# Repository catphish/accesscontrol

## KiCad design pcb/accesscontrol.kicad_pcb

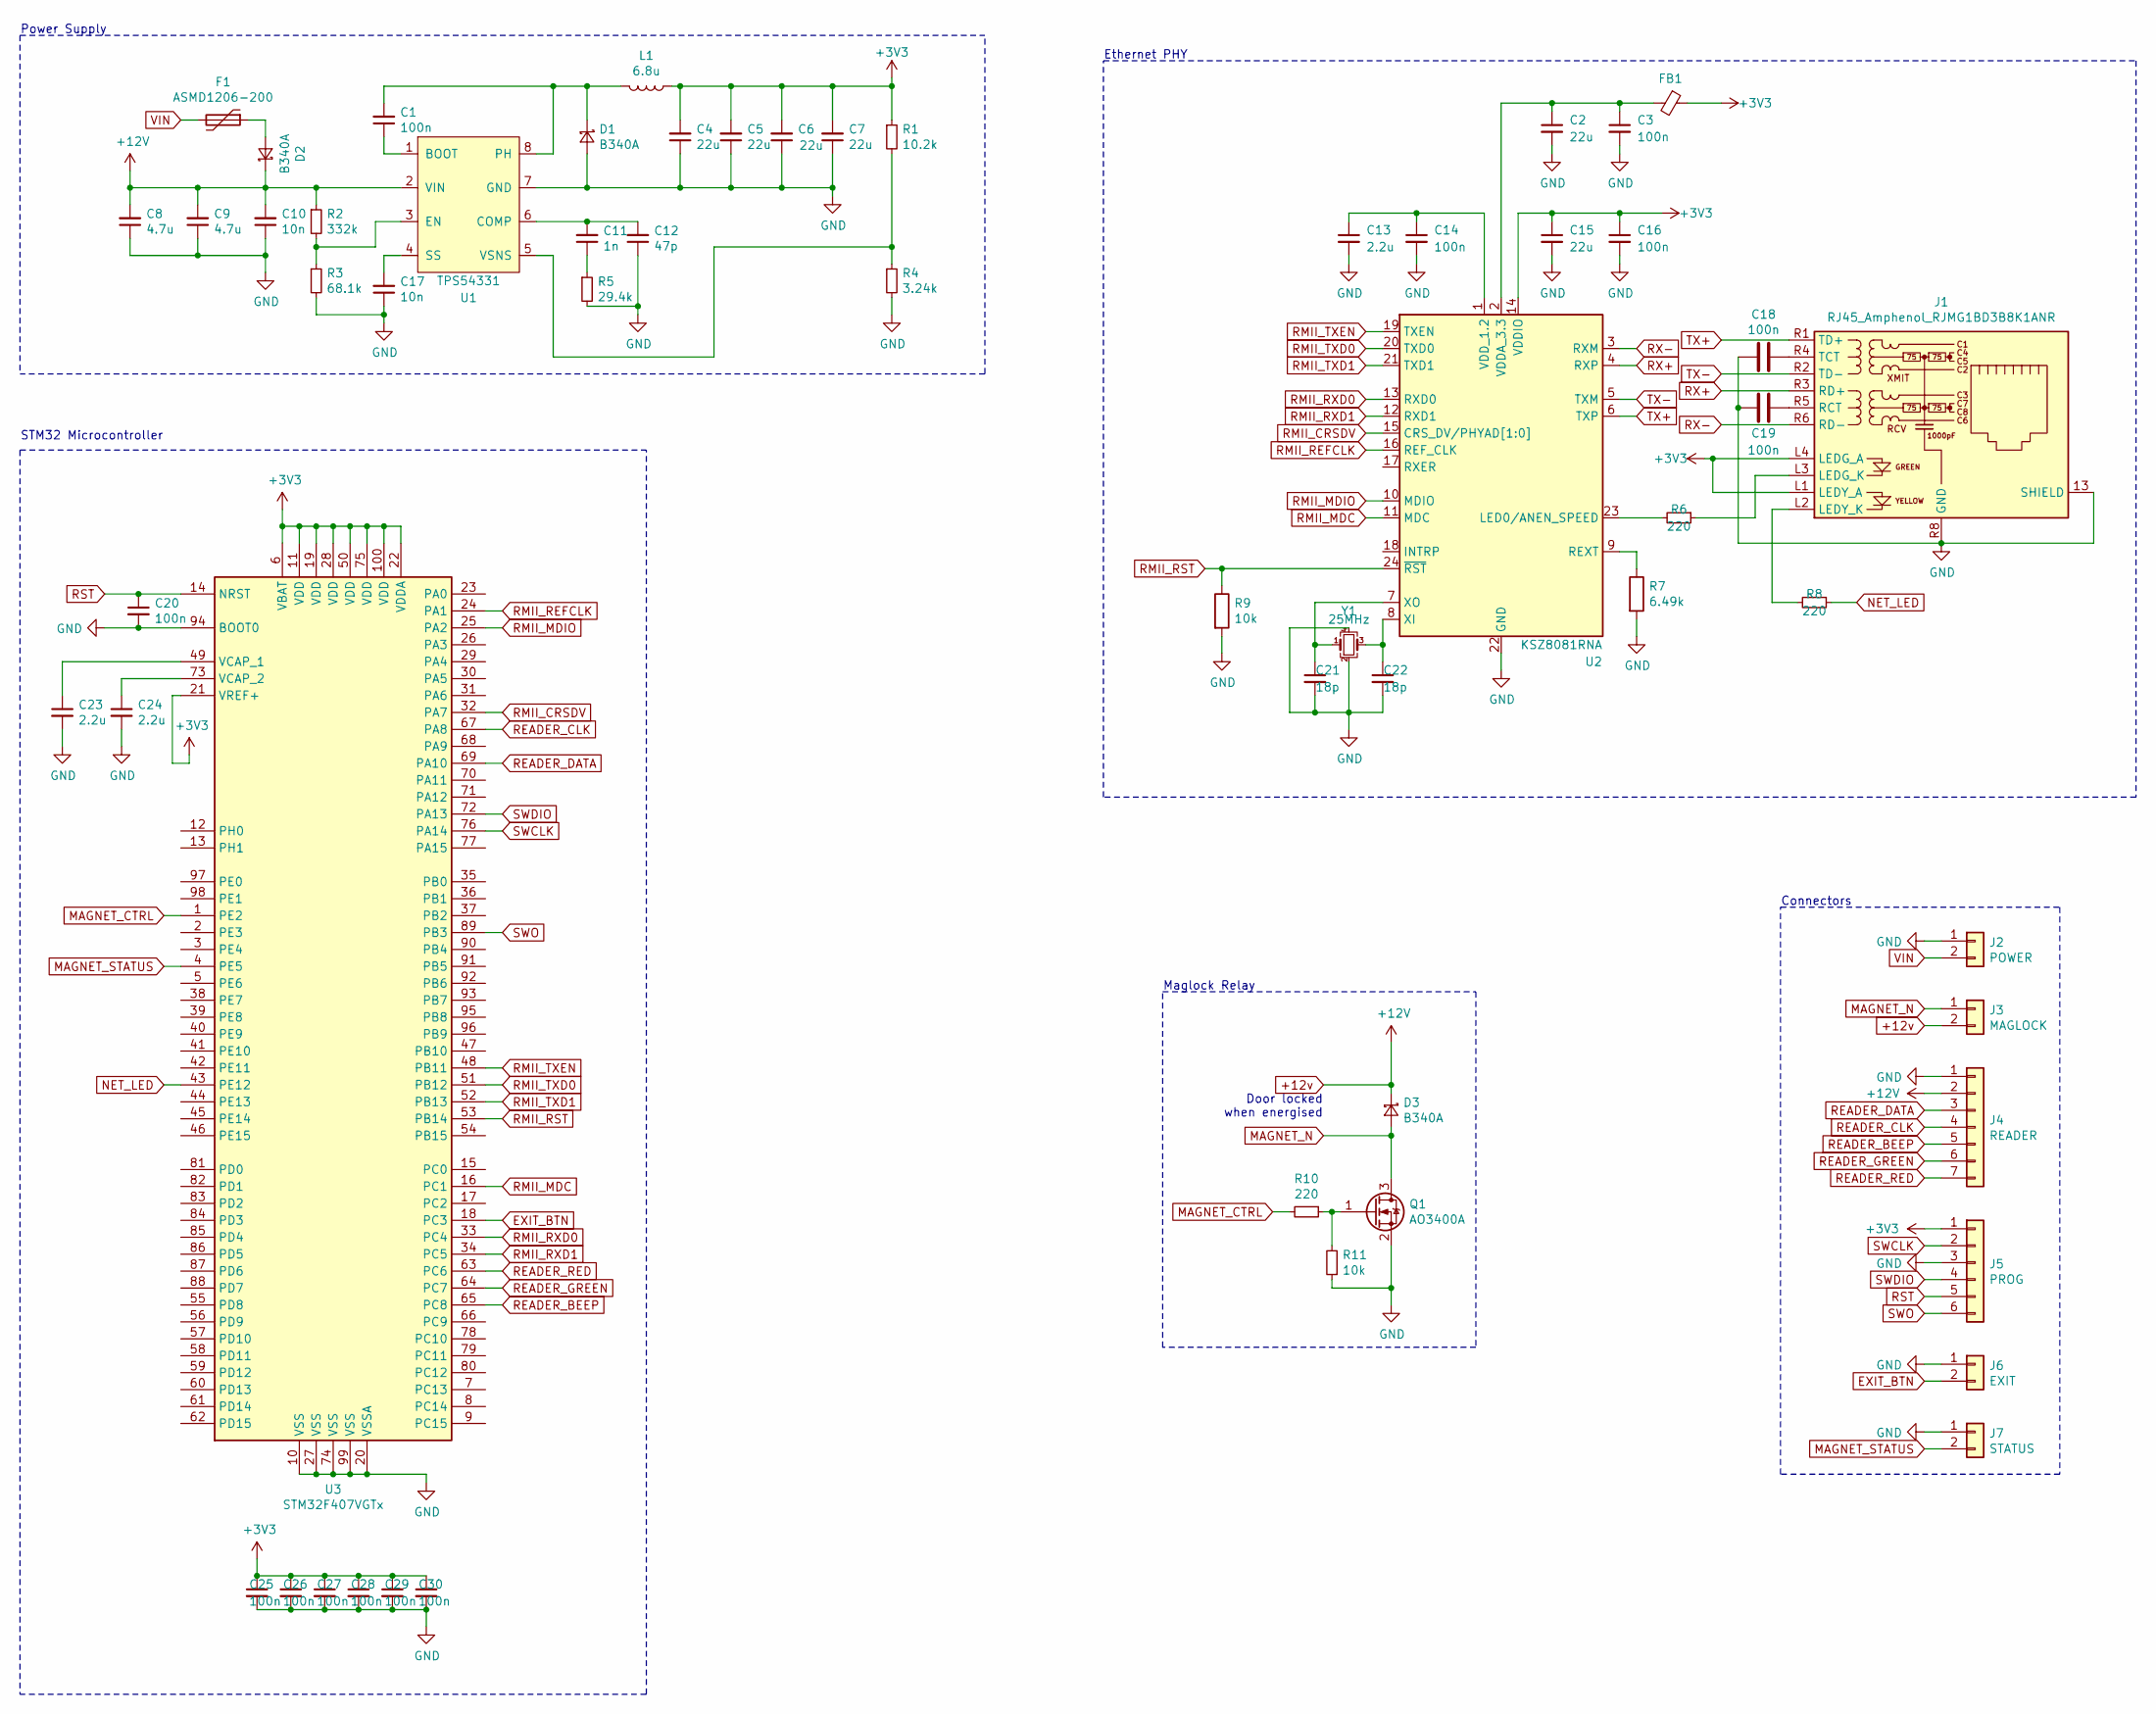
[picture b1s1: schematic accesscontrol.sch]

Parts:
C1, C3, C14, C16, C18, C19, C20, C25, C26, C27, C28, C29, C30: 100n; C_0603_1608Metric; LCSC C14663
C2, C4, C5, C6, C7, C15: 22u; C_0603_1608Metric; LCSC C59461
C8, C9: 4.7u; C_1206_3216Metric; LCSC C29823
C10, C17: 10n; C_0603_1608Metric; LCSC C57112
C11: 1n; C_0603_1608Metric; LCSC C1588
C12: 47p; C_0603_1608Metric; LCSC C1671
C13, C23, C24: 2.2u; C_0603_1608Metric; LCSC C23630
C21, C22: 18p; C_0603_1608Metric; LCSC C1647
D1, D2, D3: B340A; D_SMA; LCSC C64982
F1: ASMD1206-200; Fuse_1206_3216Metric; LCSC C135342
FB1: Ferrite_Bead_Small; L_0805_2012Metric; LCSC C1017
J1: RJ45_Amphenol_RJMG1BD3B8K1ANR
J2: POWER; TerminalBlock_RND_205-00001_1x02_P5.00mm_Horizontal
J3: MAGLOCK; TerminalBlock_RND_205-00001_1x02_P5.00mm_Horizontal
J4: READER; TerminalBlock_RND_205-00006_1x07_P5.00mm_Horizontal
J5: PROG; PinHeader_1x06_P2.54mm_Vertical
J6: EXIT; TerminalBlock_RND_205-00001_1x02_P5.00mm_Horizontal
J7: STATUS; TerminalBlock_RND_205-00001_1x02_P5.00mm_Horizontal
L1: 6.8u; L_Sunlord_MWSA0518_5.4x5.2mm; LCSC C408348
Q1: AO3400A; SOT-23; LCSC C20917
R1: 10.2k; R_0603_1608Metric; LCSC C22772
R2: 332k; R_0603_1608Metric; LCSC C23139
R3: 68.1k; R_0603_1608Metric; LCSC C25976
R4: 3.24k; R_0603_1608Metric; LCSC C22994
R5: 29.4k; R_0603_1608Metric; LCSC C22974
R6, R8, R10: 220; R_0603_1608Metric; LCSC C22962
R7: 6.49k; R_0603_1608Metric; LCSC C23088
R9, R11: 10k; R_0603_1608Metric; LCSC C25804
U1: TPS54331; SOIC-8_3.9x4.9mm_P1.27mm; LCSC C9865
U2: KSZ8081RNA; QFN-24-1EP_4x4mm_P0.5mm_EP2.6x2.6mm; LCSC C100017
U3: STM32F407VGTx; LQFP-100_14x14mm_P0.5mm; LCSC C12345
Y1: 25MHz; Crystal_SMD_3225-4Pin_3.2x2.5mm; LCSC C9006

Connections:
+3V3: C4.2, C5.2, C6.2, C7.2, C15.1, C16.1, C25.1, C26.1, C27.1, C28.1, C29.1, C30.1, FB1.1, J1.L1 (LEDY_A), J1.L4 (LEDG_A), J5.1, L1.1, R1.1, U2.14 (VDDIO), U3.6 (VBAT), U3.11 (VDD), U3.19 (VDD), U3.21 (VREF+), U3.22 (VDDA), U3.28 (VDD), U3.50 (VDD), U3.75 (VDD), U3.100 (VDD)
+12v: C8.2, C9.2, C10.2, D2.1 (K), D3.1 (K), J3.2, J4.2, R2.1, U1.2 (VIN)
EXIT_BTN: J6.2, U3.18 (PC3)
GND: C2.2, C3.2, C4.1, C5.1, C6.1, C7.1, C8.1, C9.1, C10.1, C12.1, C13.2, C14.2, C15.2, C16.2, C17.1, C18.2, C19.2, C20.2, C21.2, C22.2, C23.2, C24.2, C25.2, C26.2, C27.2, C28.2, C29.2, C30.2, D1.2 (A), J1.13 (SHIELD), J1.R8 (GND), J2.1, J4.1, J5.3, J6.1, J7.1, Q1.2 (S), R3.2, R4.2, R5.2, R7.2, R9.2, R11.1, U1.7 (GND), U2.22 (GND), U2.25 (GND), U3.10 (VSS), U3.20 (VSSA), U3.27 (VSS), U3.74 (VSS), U3.94 (BOOT0), U3.99 (VSS), Y1.2, Y1.4
MAGNET_CTRL: R10.2, U3.1 (PE2)
MAGNET_N: D3.2 (A), J3.1, Q1.3 (D)
MAGNET_STATUS: J7.2, U3.4 (PE5)
NET_LED: R8.1, U3.43 (PE12)
unnamed: C1.1, U1.1 (BOOT)
unnamed: C1.2, D1.1 (K), L1.2, U1.8 (PH)
unnamed: C2.1, C3.1, FB1.2, U2.2 (VDDA_3.3)
unnamed: C11.1, R5.1
unnamed: C11.2, C12.2, U1.6 (COMP)
unnamed: C13.1, C14.1, U2.1 (VDD_1.2)
unnamed: C17.2, U1.4 (SS)
unnamed: C18.1, J1.R4 (TCT)
unnamed: C19.1, J1.R5 (RCT)
unnamed: C21.1, U2.7 (XO), Y1.1
unnamed: C22.1, U2.8 (XI), Y1.3
unnamed: C23.1, U3.49 (VCAP_1)
unnamed: C24.1, U3.73 (VCAP_2)
unnamed: D2.2 (A), F1.1
unnamed: J1.L2 (LEDY_K), R8.2
unnamed: J1.L3 (LEDG_K), R6.1
unnamed: Q1.1 (G), R10.1, R11.2
unnamed: R1.2, R4.1, U1.5 (VSNS)
unnamed: R2.2, R3.1, U1.3 (EN)
unnamed: R6.2, U2.23 (LED0/ANEN_SPEED)
unnamed: R7.1, U2.9 (REXT)
READER_BEEP: J4.5, U3.65 (PC8)
READER_CLK: J4.4, U3.67 (PA8)
READER_DATA: J4.3, U3.69 (PA10)
READER_GREEN: J4.6, U3.64 (PC7)
READER_RED: J4.7, U3.63 (PC6)
RMII_CRSDV: U2.15 (CRS_DV/PHYAD[1:0]), U3.32 (PA7)
RMII_MDC: U2.11 (MDC), U3.16 (PC1)
RMII_MDIO: U2.10 (MDIO), U3.25 (PA2)
RMII_REFCLK: U2.16 (REF_CLK), U3.24 (PA1)
RMII_RST: R9.1, U2.24 (~RST), U3.53 (PB14)
RMII_RXD0: U2.13 (RXD0), U3.33 (PC4)
RMII_RXD1: U2.12 (RXD1), U3.34 (PC5)
RMII_TXD0: U2.20 (TXD0), U3.51 (PB12)
RMII_TXD1: U2.21 (TXD1), U3.52 (PB13)
RMII_TXEN: U2.19 (TXEN), U3.48 (PB11)
RST: C20.1, J5.5, U3.14 (NRST)
RX+: J1.R3 (RD+), U2.4 (RXP)
RX-: J1.R6 (RD-), U2.3 (RXM)
SWCLK: J5.2, U3.76 (PA14)
SWDIO: J5.4, U3.72 (PA13)
SWO: J5.6, U3.89 (PB3)
TX+: J1.R1 (TD+), U2.6 (TXP)
TX-: J1.R2 (TD-), U2.5 (TXM)
VIN: F1.2, J2.2

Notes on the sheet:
Power Supply
STM32 Microcontroller
Ethernet PHY
Connectors
Maglock Relay
Door locked when energised

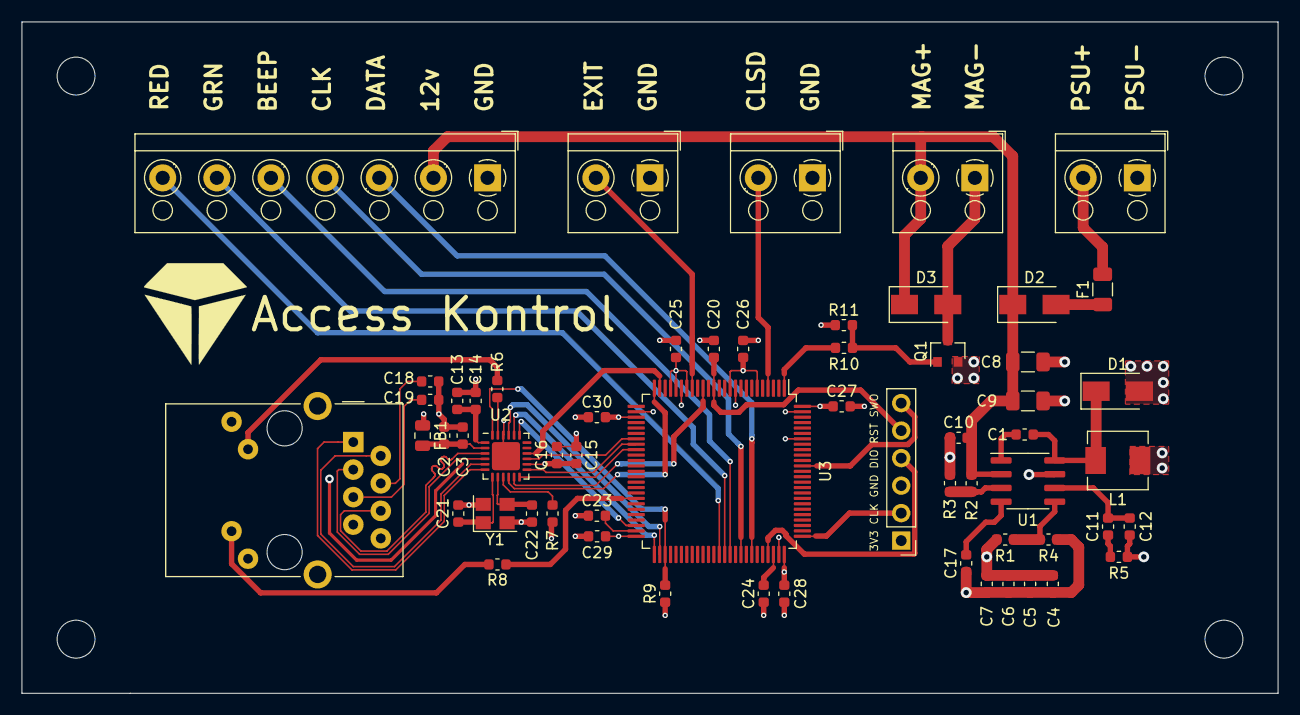
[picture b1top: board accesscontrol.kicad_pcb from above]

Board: 4 copper layers, 116.0 x 62.0 mm, 59 parts (0 on the bottom side), 53 nets.

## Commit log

2020-04-25 just a backup of WIP
2020-04-25 more WIP
2020-04-26 work in progress on dhcp, tidying
2020-05-01 largely finish ip stack
2020-05-02 add cryto libraries, use library memory functions
2020-05-10 various cloud network / security work
2020-05-13 card reader innit
2020-05-23 more network and server stuff
2020-05-24 reader LEDs
2020-06-21 add exit button, remove support for dev board
2020-06-21 add hardware
